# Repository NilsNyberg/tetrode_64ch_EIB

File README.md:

# tetrode_64ch_EIB
Gerber and build files for electric interface board custom-made for 64ch small tetrode drive. For use with Axona mouse 3D printable Delrin legs (files to be added)

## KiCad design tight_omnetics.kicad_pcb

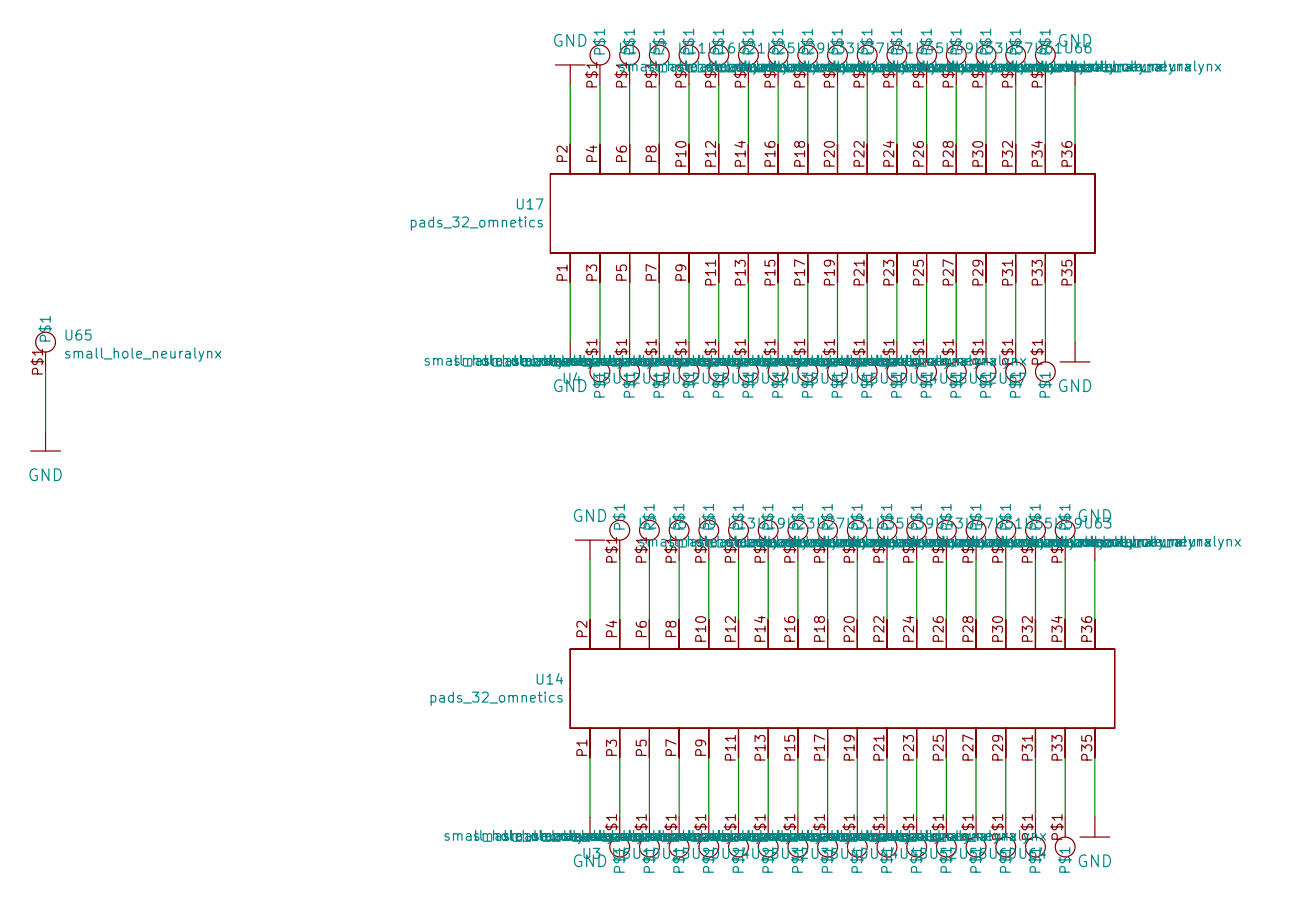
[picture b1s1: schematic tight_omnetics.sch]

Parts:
U1, U2, U3, U4, U5, U6, U7, U8, U9, U10, U11, U12, U13, U15, U16, U18, U19, U20, U21, U22, U23, U24, U25, U26, U27, U28, U29, U30, U31, U32, U33, U34, U35, U36, U37, U38, U39, U40, U41, U42, U43, U44, U45, U46, U47, U48, U49, U50, U51, U52, U53, U54, U55, U56, U57, U58, U59, U60, U61, U62, U63, U64, U65, U66, U67: small_hole_neuralynx; pin_for_neuralynx
U14, U17: pads_32_omnetics; through_hole_for_omnetics

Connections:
GND: U14.P1, U14.P2, U14.P35, U14.P36, U17.P1, U17.P2, U17.P35, U17.P36, U65.P$1
unnamed: U1.P$1, U17.P4
unnamed: U10.P$1, U14.P7
unnamed: U11.P$1, U17.P8
unnamed: U12.P$1, U17.P7
unnamed: U13.P$1, U14.P10
unnamed: U3.P$1, U14.P3
unnamed: U2.P$1, U14.P4
unnamed: U6.P$1, U14.P5
unnamed: U5.P$1, U14.P6
unnamed: U9.P$1, U14.P8
unnamed: U14.P9, U15.P$1
unnamed: U14.P11, U20.P$1
unnamed: U14.P12, U19.P$1
unnamed: U14.P13, U24.P$1
unnamed: U14.P14, U23.P$1
unnamed: U14.P15, U28.P$1
unnamed: U14.P16, U27.P$1
unnamed: U14.P17, U32.P$1
unnamed: U14.P18, U31.P$1
unnamed: U14.P19, U36.P$1
unnamed: U14.P20, U35.P$1
unnamed: U14.P21, U40.P$1
unnamed: U14.P22, U39.P$1
unnamed: U14.P23, U44.P$1
unnamed: U14.P24, U43.P$1
unnamed: U14.P25, U48.P$1
unnamed: U14.P26, U47.P$1
unnamed: U14.P27, U52.P$1
unnamed: U14.P28, U51.P$1
unnamed: U14.P29, U56.P$1
unnamed: U14.P30, U55.P$1
unnamed: U14.P31, U60.P$1
unnamed: U14.P32, U59.P$1
unnamed: U14.P33, U64.P$1
unnamed: U14.P34, U63.P$1
unnamed: U16.P$1, U17.P10
unnamed: U4.P$1, U17.P3
unnamed: U8.P$1, U17.P5
unnamed: U7.P$1, U17.P6
unnamed: U17.P9, U18.P$1
unnamed: U17.P11, U22.P$1
unnamed: U17.P12, U21.P$1
unnamed: U17.P13, U26.P$1
unnamed: U17.P14, U25.P$1
unnamed: U17.P15, U30.P$1
unnamed: U17.P16, U29.P$1
unnamed: U17.P17, U34.P$1
unnamed: U17.P18, U33.P$1
unnamed: U17.P19, U38.P$1
unnamed: U17.P20, U37.P$1
unnamed: U17.P21, U42.P$1
unnamed: U17.P22, U41.P$1
unnamed: U17.P23, U46.P$1
unnamed: U17.P24, U45.P$1
unnamed: U17.P25, U50.P$1
unnamed: U17.P26, U49.P$1
unnamed: U17.P27, U54.P$1
unnamed: U17.P28, U53.P$1
unnamed: U17.P29, U58.P$1
unnamed: U17.P30, U57.P$1
unnamed: U17.P31, U62.P$1
unnamed: U17.P32, U61.P$1
unnamed: U17.P33, U67.P$1
unnamed: U17.P34, U66.P$1

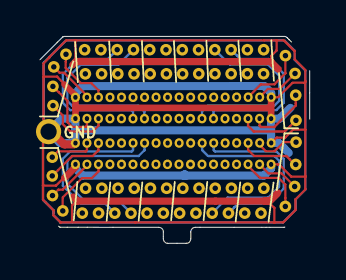
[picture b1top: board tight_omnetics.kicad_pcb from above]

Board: 4 copper layers, 15.0 x 11.5 mm, 67 parts (0 on the bottom side), 65 nets.
